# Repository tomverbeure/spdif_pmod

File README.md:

# S/PDIF Optical Output PMOD

* [My blog post about this project](http://tomverbeure.github.io/2021/01/18t/SPDIF-Output-PMOD.html)

Features:

* S/PDIF optical output (TOSLINK)
* 4 GPIOs

The total cost is around ~$30:

* PCB (JLCPCB): $2 + $14 shipping (for 5 PCBs)
* TOSLink connecter: $10
* All the rest: ~$4

## SPDIF Board

The board was designed with [KiCAD](https://kicad.org/).

**Schematic**

[Schematic in PDF format](pcb/pmod_spdif/pmod_spdif.pdf)

**PCB**

**Component list**

## Example Design

The PMOD was tested on an [Intel Max10 development board](https://www.intel.com/content/www/us/en/programmable/products/boards_and_kits/dev-kits/altera/max-10-fpga-development-kit.html), 
but it should be trivial to make it work on any FPGA board that has a PMOD connector.

The [RTL](blob/main/fpga/spinal/src/main/scala/spdif/SpdifOut.scala) is written in 
[SpinalHDL](https://spinalhdl.github.io/SpinalDoc-RTD/), which gets converted into Verilog.

There's also a small [testbench](tree/main/fpga/tb/spdif) that uses 
[CXXRTL](https://tomverbeure.github.io/2020/08/08/CXXRTL-the-New-Yosys-Simulation-Backend.html) 
to simulate the whole thing. The testbench is not self-checking. You'll need to eyeball the waveforms to verify
that things are working...

The Max10 design uses a PLL to create a 6.144MHz clock out of the 50MHz oscillator clock.

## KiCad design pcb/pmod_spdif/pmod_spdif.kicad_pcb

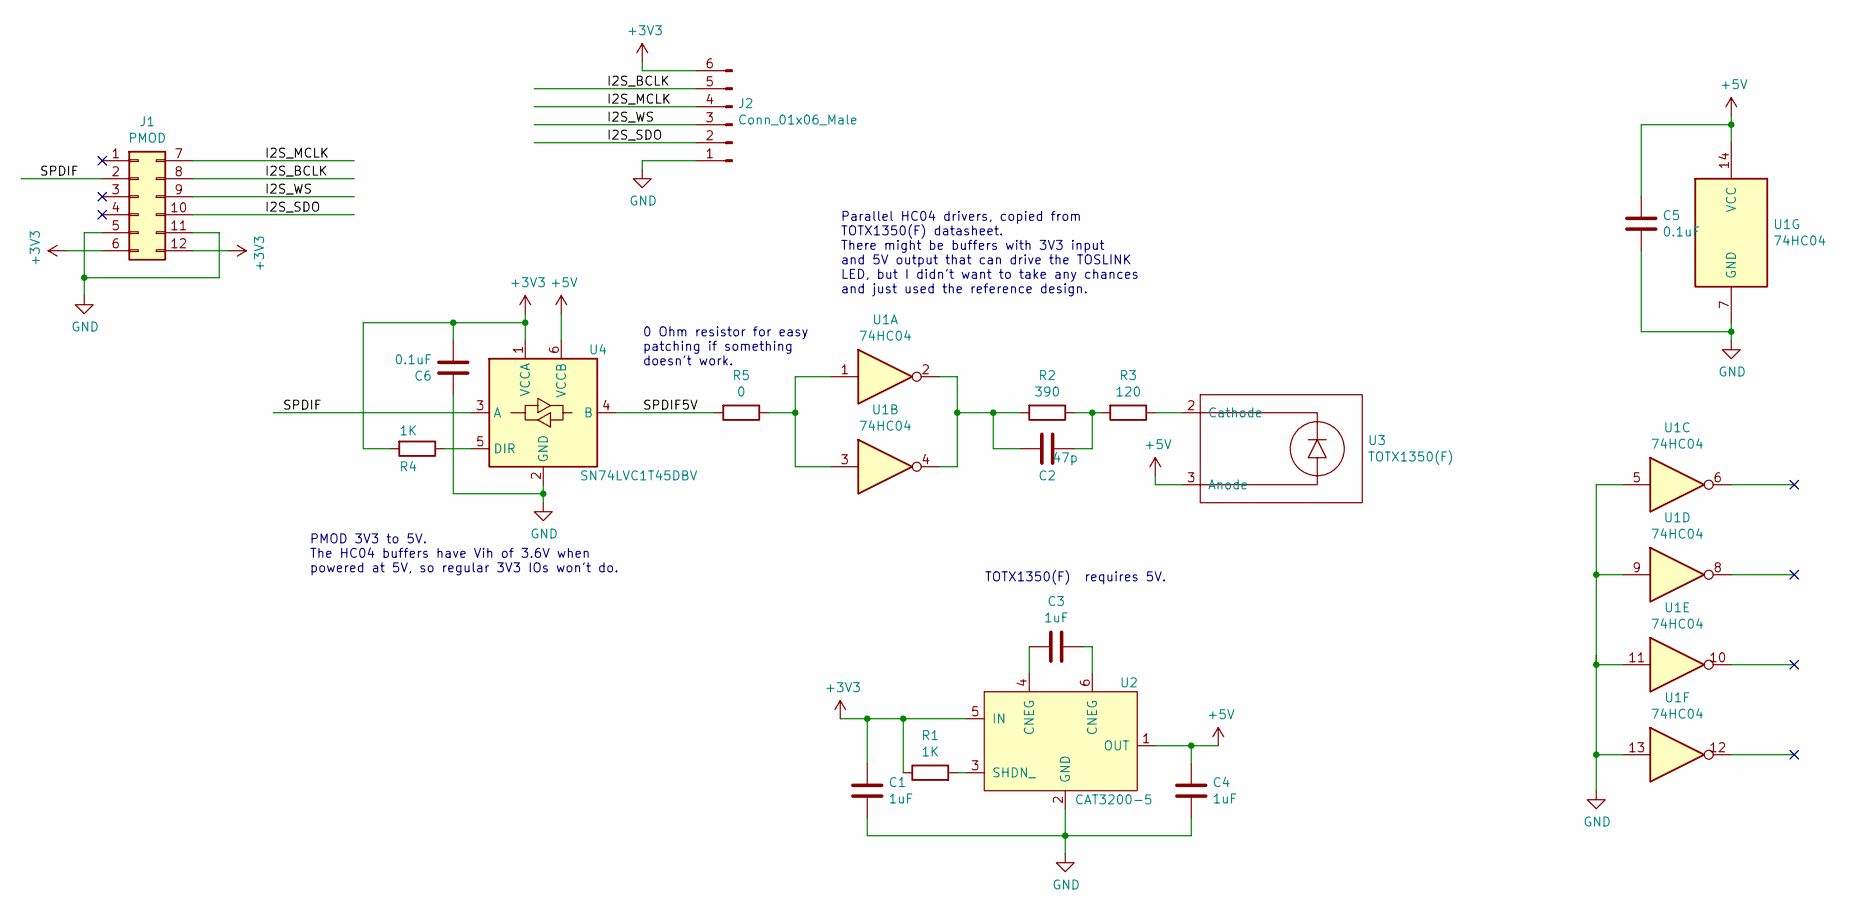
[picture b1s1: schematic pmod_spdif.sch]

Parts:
C1, C3, C4: 1uF; C_0603_1608Metric_Pad1.05x0.95mm_HandSolder
C2: 47p; C_0603_1608Metric_Pad1.05x0.95mm_HandSolder
C5, C6: 0.1uF; C_0603_1608Metric_Pad1.05x0.95mm_HandSolder
J1: PMOD; PMOD_Male
J2: Conn_01x06_Male; PinHeader_1x06_P2.54mm_Vertical
R1, R4: 1K; R_0603_1608Metric_Pad1.05x0.95mm_HandSolder
R2: 390; R_0603_1608Metric_Pad1.05x0.95mm_HandSolder
R3: 120; R_0603_1608Metric_Pad1.05x0.95mm_HandSolder
R5: 0; R_0603_1608Metric_Pad1.05x0.95mm_HandSolder
U1: 74HC04; SOIC-14_3.9x8.7mm_P1.27mm
U2: CAT3200-5; TSOT-23-6_HandSoldering
U3: TOTX1350(F); TOTXA1350(F)
U4: SN74LVC1T45DBV; SOT-23-6

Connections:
+3V3: C1.1, C6.2, J1.6, J1.12, J2.6, R1.1, R4.2, U2.5 (IN), U4.1 (VCCA)
+5V: C4.1, C5.1, U1.14 (VCC), U2.1 (OUT), U3.3 (Anode), U4.6 (VCCB)
/I2S_BCLK: J1.8, J2.5
/I2S_MCLK: J1.7, J2.4
/I2S_SDO: J1.10, J2.2
/I2S_WS: J1.9, J2.3
/SPDIF: J1.2, U4.3 (A)
/SPDIF5V: R5.2, U4.4 (B)
GND: C1.2, C4.2, C5.2, C6.1, J1.5, J1.11, J2.1, U1.5, U1.7 (GND), U1.9, U1.11, U1.13, U2.2 (GND), U4.2 (GND)
unnamed: C2.1, R2.2, U1.2, U1.4
unnamed: C2.2, R2.1, R3.2
unnamed: C3.1, U2.6 (CNEG)
unnamed: C3.2, U2.4 (CNEG)
unnamed: R1.2, U2.3 (SHDN_)
unnamed: R3.1, U3.2 (Cathode)
unnamed: R4.1, U4.5 (DIR)
unnamed: R5.1, U1.1, U1.3

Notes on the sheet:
Parallel HC04 drivers, copied from TOTX1350(F) datasheet. There might be buffers with 3V3 input and 5V output that can drive the TOSLINK LED, but I didn't want to take any chances and just used the reference design.
0 Ohm resistor for easy patching if something doesn't work.
TOTX1350(F) requires 5V.
PMOD 3V3 to 5V. The HC04 buffers have Vih of 3.6V when powered at 5V, so regular 3V3 IOs won't do.

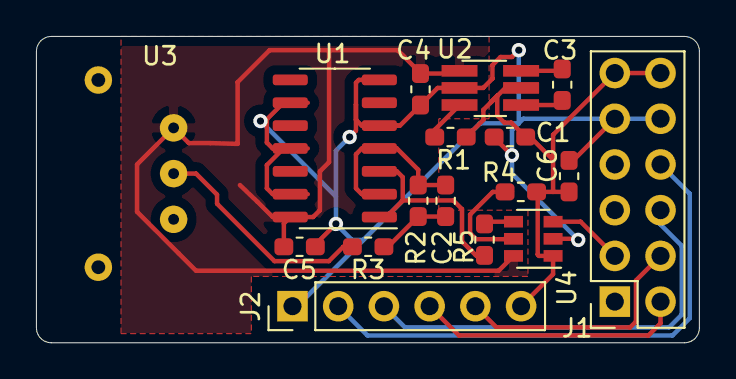
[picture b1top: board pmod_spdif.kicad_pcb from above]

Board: 2 copper layers, 36.8 x 17.0 mm, 17 parts (0 on the bottom side), 17 nets.

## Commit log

2021-01-13 Initial.
2021-01-13 Add photo.
2021-01-13 Add some photos.
2021-01-13 Minor edits.
2021-01-15 pmod_spdif v2. Only cosmetic changes.
2021-01-15 Add digikey component list.
2021-01-18 Move images.
2021-01-18 Spdif test project.
2021-01-18 Reduce RTL to Spdif example only.
2021-01-18 Make Max10 example work.
2021-01-18 Make testbench work again.
2021-01-18 Simulation README.
2021-01-18 Update link to pictures.
2021-01-18 Update documentation.
2021-01-18 Add missing images.
2021-01-18 Add URLs.
2021-01-18 Text has been moved to blog post.
2021-01-18 Add generated verilog.
2021-01-20 colorlight example.
2021-01-20 PLL outputs 12.288 MHz now. Change clock divider accordingly.
2021-01-23 Add SYSCONFIG COMPRESS_CONFIG=ON.
2021-01-23 Really add SYSCONFIG COMPRESS_CONFIG=ON;
2021-01-30 Use ecpdap for programming and flashing.
